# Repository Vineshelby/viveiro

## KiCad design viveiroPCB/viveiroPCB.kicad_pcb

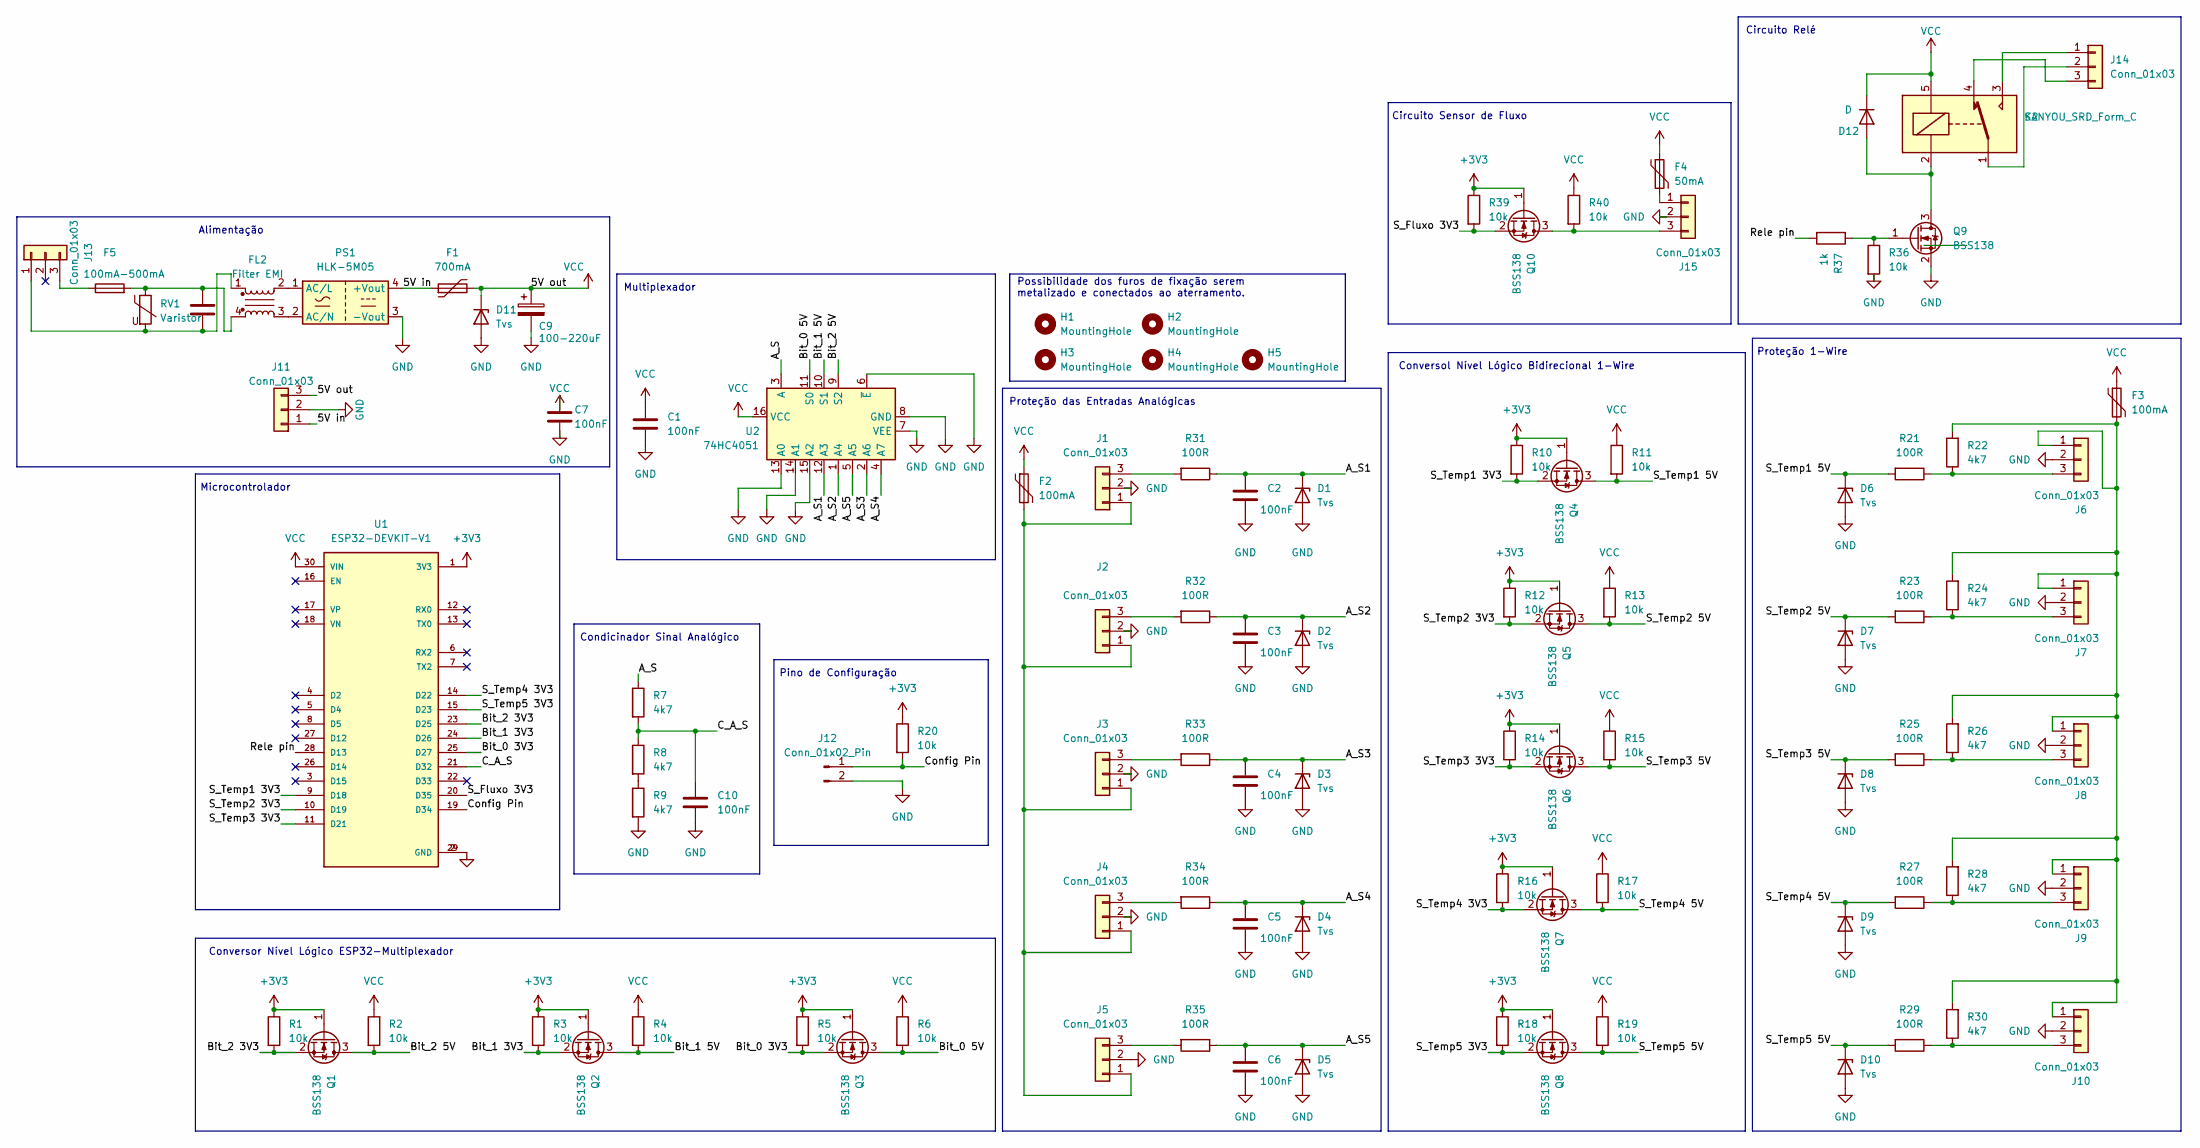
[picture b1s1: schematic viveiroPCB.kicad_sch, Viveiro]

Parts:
C1, C2, C3, C4, C5, C6, C7, C10: 100nF; C_0805_2012Metric
C8: 0.1uF; C_Rect_L13.5mm_W5.0mm_P10.00mm_FKS3_FKP3_MKS4
C9: 100-220uF; CP_Radial_D10.0mm_P3.80mm
D1, D2, D3, D4, D5, D6, D7, D8, D9, D10, D11: Tvs; D_SMB
D12: D; D_SMA
F1: 700mA; Fuse_1206_3216Metric
F2, F3: 100mA; Fuse_1206_3216Metric
F4: 50mA; Fuse_1206_3216Metric
F5: 100mA-500mA; Fuseholder_Cylinder-5x20mm_Schurter_0031_8201_Horizontal_Op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
FL2: Filter EMI; uu9.8
H1, H2, H3, H4, H5: MountingHole; MountingHole_3.2mm_M3_DIN965
J1, J2, J3, J4, J5, J6, J7, J8, J9, J10, J15: Conn_01x03; Molex_KK-254_AE-6410-03A_1x03_P2.54mm_Vertical
J11, J13, J14: Conn_01x03; PhoenixContact_MSTBA_2,5_3-G-5,08_1x03_P5.08mm_Horizontal
J12: Conn_01x02_Pin; PinHeader_1x02_P2.54mm_Vertical
K2: SANYOU_SRD_Form_C; Relay_SPDT_SANYOU_SRD_Series_Form_C
PS1: HLK-5M05; Converter_ACDC_Hi-Link_HLK-5Mxx
Q1, Q2, Q3, Q4, Q5, Q6, Q7, Q8, Q9, Q10: BSS138; SOT-23
R1, R2, R3, R4, R5, R6, R10, R11, R12, R13, R14, R15, R16, R17, R18, R19, R20, R36, R39, R40: 10k; R_0805_2012Metric
R7, R8, R9, R22, R24, R26, R28, R30: 4k7; R_0805_2012Metric
R21, R23, R25, R27, R29, R31, R32, R33, R34, R35: 100R; R_1206_3216Metric
R37: 1k; R_0805_2012Metric
RV1: Varistor; RV_Disc_D12mm_W7.1mm_P7.5mm
U1: ESP32-DEVKIT-V1; MODULE_ESP32_DEVKIT_V1; PARTREV N/A
U2: 74HC4051; SO-16_3.9x9.9mm_P1.27mm

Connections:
+3V3: Q1.1 (G), Q2.1 (G), Q3.1 (G), Q4.1 (G), Q5.1 (G), Q6.1 (G), Q7.1 (G), Q8.1 (G), Q10.1 (G), R1.1, R3.1, R5.1, R10.1, R12.1, R14.1, R16.1, R18.1, R20.1, R39.1, U1.1 (3V3)
/5V in: F1.1, J11.1, PS1.4 (+Vout)
/A_S: R7.1, U2.3 (A)
/A_S1: C2.1, D1.1 (K), R31.1, U2.12 (A3)
/A_S2: C3.1, D2.1 (K), R32.1, U2.1 (A4)
/A_S3: C4.1, D3.1 (K), R33.1, U2.2 (A6)
/A_S4: C5.1, D4.1 (K), R34.1, U2.4 (A7)
/A_S5: C6.1, D5.1 (K), R35.1, U2.5 (A5)
/Bit_0 3V3: Q3.2 (S), R5.2, U1.25 (D27)
/Bit_0 5V: Q3.3 (D), R6.2, U2.11 (S0)
/Bit_1 3V3: Q2.2 (S), R3.2, U1.24 (D26)
/Bit_1 5V: Q2.3 (D), R4.2, U2.10 (S1)
/Bit_2 3V3: Q1.2 (S), R1.2, U1.23 (D25)
/Bit_2 5V: Q1.3 (D), R2.2, U2.9 (S2)
/C_A_S: C10.1, R7.2, R8.1, U1.21 (D32)
/Config Pin: J12.1, R20.2, U1.19 (D34)
/Rele pin: R37.2, U1.28 (D13)
/S_Fluxo 3V3: Q10.2 (S), R39.2, U1.20 (D35)
/S_Temp1 3V3: Q4.2 (S), R10.2, U1.9 (D18)
/S_Temp1 5V: D6.1 (K), Q4.3 (D), R11.2, R21.2
/S_Temp2 3V3: Q5.2 (S), R12.2, U1.10 (D19)
/S_Temp2 5V: D7.1 (K), Q5.3 (D), R13.2, R23.2
/S_Temp3 3V3: Q6.2 (S), R14.2, U1.11 (D21)
/S_Temp3 5V: D8.1 (K), Q6.3 (D), R15.2, R25.2
/S_Temp4 3V3: Q7.2 (S), R16.2, U1.14 (D22)
/S_Temp4 5V: D9.1 (K), Q7.3 (D), R17.2, R27.2
/S_Temp5 3V3: Q8.2 (S), R18.2, U1.15 (D23)
/S_Temp5 5V: D10.1 (K), Q8.3 (D), R19.2, R29.2
GND: C1.2, C2.2, C3.2, C4.2, C5.2, C6.2, C7.2, C9.2, C10.2, D1.2 (A), D2.2 (A), D3.2 (A), D4.2 (A), D5.2 (A), D6.2 (A), D7.2 (A), D8.2 (A), D9.2 (A), D10.2 (A), D11.2 (A), J1.2, J2.2, J3.2, J4.2, J5.2, J6.2, J7.2, J8.2, J9.2, J10.2, J11.2, J12.2, J15.2, PS1.3 (-Vout), Q9.2 (S), R9.2, R36.2, U1.2 (GND), U1.29 (GND), U2.6 (~E), U2.7 (VEE), U2.8 (GND), U2.13 (A0), U2.14 (A1), U2.15 (A2)
unnamed: C8.1, F5.2, FL2.4, RV1.1
unnamed: D12.2 (A), K2.2, Q9.3 (D)
unnamed: F2.2, J1.1, J2.1, J3.1, J4.1, J5.1
unnamed: J1.3, R31.2
unnamed: J2.3, R32.2
unnamed: J3.3, R33.2
unnamed: J4.3, R34.2
unnamed: J5.3, R35.2
unnamed: J6.3, R21.1, R22.1
unnamed: J7.3, R23.1, R24.1
unnamed: J8.3, R25.1, R26.1
unnamed: J9.3, R27.1, R28.1
unnamed: F3.2, J6.1, J7.1, J8.1, J9.1, J10.1, R22.2, R24.2, R26.2, R28.2, R30.2
unnamed: J10.3, R29.1, R30.1
unnamed: C8.2, FL2.1, J13.1, RV1.2
unnamed: F5.1, J13.3
unnamed: J14.1, K2.3
unnamed: J14.2, K2.1
unnamed: J14.3, K2.4
unnamed: F4.2, J15.1
unnamed: J15.3, Q10.3 (D), R40.2
unnamed: FL2.2, PS1.1 (AC/L)
unnamed: FL2.3, PS1.2 (AC/N)
unnamed: Q9.1 (G), R36.1, R37.1
unnamed: R8.2, R9.1
VCC: C1.1, C7.1, C9.1, D11.1 (K), D12.1 (K), F1.2, F2.1, F3.1, F4.1, J11.3, K2.5, R2.1, R4.1, R6.1, R11.1, R13.1, R15.1, R17.1, R19.1, R40.1, U1.30 (VIN), U2.16 (VCC)

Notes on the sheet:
Microcontrolador
Proteção das Entradas Analógicas
Multiplexador
Proteção 1-Wire
Circuito Relé
Alimentação
Possibilidade dos furos de fixação serem metalizado e conectados ao aterramento.
Circuito Sensor de Fluxo
Conversol Nível Lógico Bidirecional 1-Wire
Conversor Nível Lógico ESP32-Multiplexador
Pino de Configuração
Condicinador Sinal Analógico

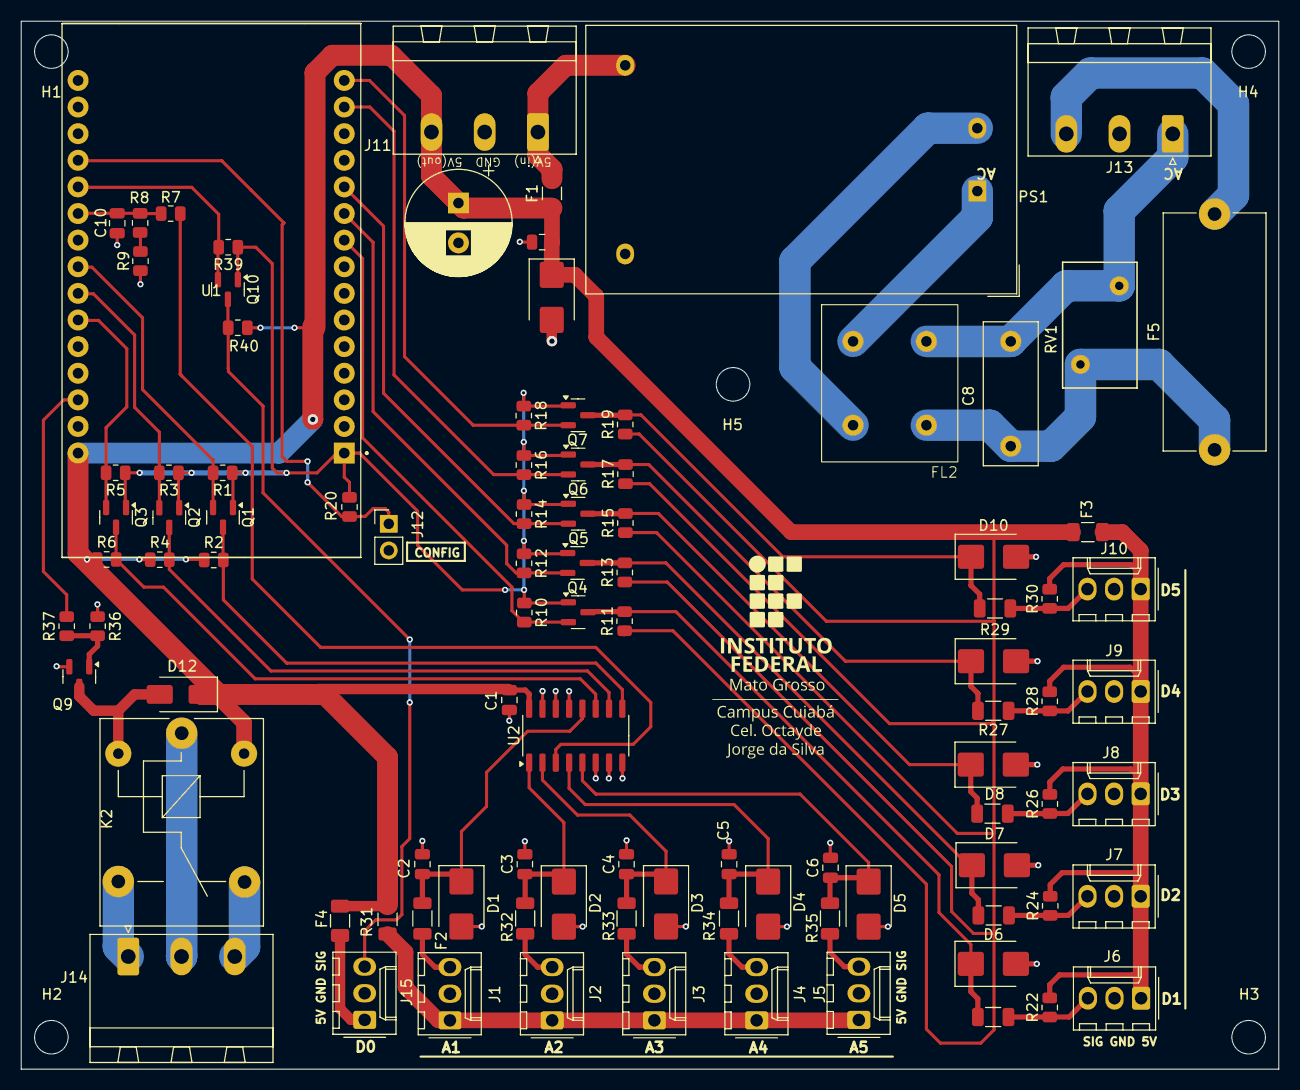
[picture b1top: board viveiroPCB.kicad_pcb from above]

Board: 2 copper layers, 120.0 x 100.0 mm, 102 parts (0 on the bottom side), 55 nets.

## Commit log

2025-01-22 remove
2025-01-24 changing folder name
2025-01-24 gitignore organization
2025-01-24 gitignore edit
2025-01-24 moving to platformio
